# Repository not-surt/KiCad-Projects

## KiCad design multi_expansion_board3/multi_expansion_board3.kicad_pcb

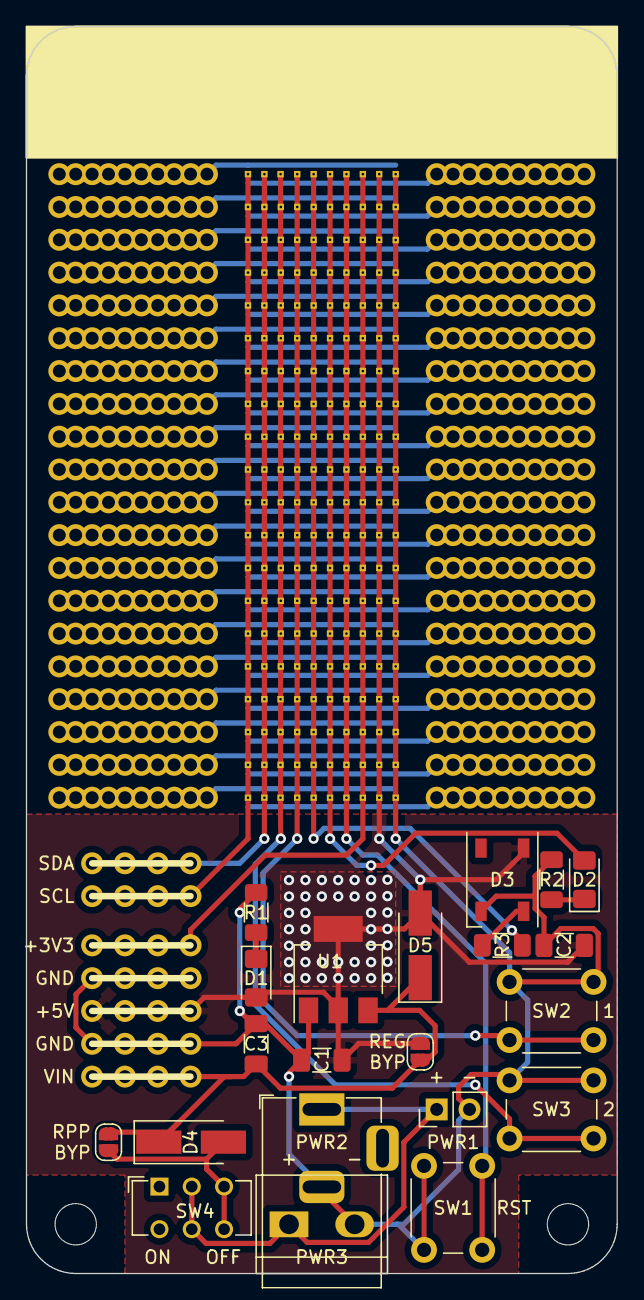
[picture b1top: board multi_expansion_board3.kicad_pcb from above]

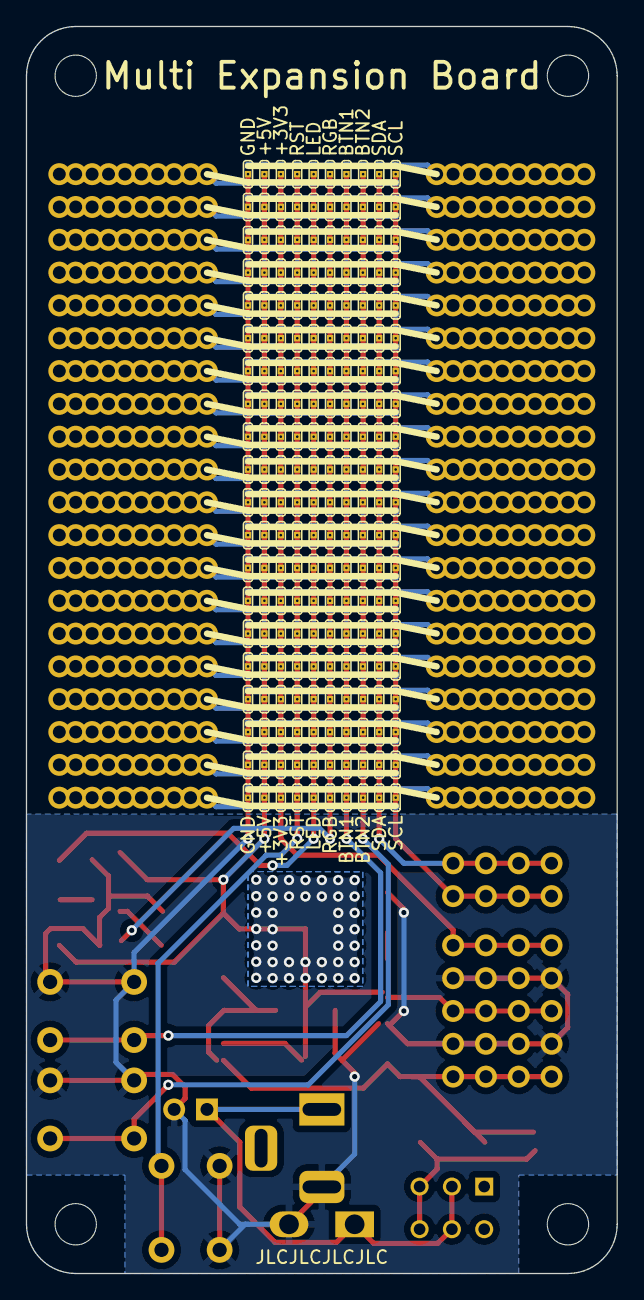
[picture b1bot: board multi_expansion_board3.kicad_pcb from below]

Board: 2 copper layers, 45.7 x 96.5 mm, 248 parts (200 on the bottom side), 56 nets.

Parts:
C1: 0.1uF; C_1206_3216Metric_Pad1.33x1.80mm_HandSolder
C2, C3: 10uF; C_1206_3216Metric_Pad1.33x1.80mm_HandSolder
D1, D2: LED; LED_1206_3216Metric_Pad1.42x1.75mm_HandSolder
D3: WS2812B; LED_WS2812B_PLCC4_5.0x5.0mm_P3.2mm
D4, D5: D; D_SMA_Handsoldering
J1, J2, J3, J4, J5, J6, J7, J8, J9, J10, J11, J12, J13, J14, J15, J16, J17, J18, J19, J20: Conn_01x20; PinHeader_1x20_P2.54mm_Vertical_No_Silk
J21, J22, J23, J24, J25, J26, J27: Conn_01x04; PinHeader_1x04_P2.54mm_Vertical_No_Silk
JP1, JP2: SolderJumper_2_Open; SolderJumper-2_P1.3mm_Open_RoundedPad1.0x1.5mm
JP3, JP4, JP5, JP6, JP7, JP8, JP9, JP10, JP11, JP12, JP13, JP14, JP15, JP16, JP17, JP18, JP19, JP20, JP21, JP22, JP23, JP24, JP25, JP26, JP27, JP28, JP29, JP30, JP31, JP32, JP33, JP34, JP35, JP36, JP37, JP38, JP39, JP40, JP41, JP42, JP43, JP44, JP45, JP46, JP47, JP48, JP49, JP50, JP51, JP52, JP53, JP54, JP55, JP56, JP57, JP58, JP59, JP60, JP61, JP62, JP63, JP64, JP65, JP66, JP67, JP68, JP69, JP70, JP71, JP72, JP73, JP74, JP75, JP76, JP77, JP78, JP79, JP80, JP81, JP82, JP83, JP84, JP85, JP86, JP87, JP88, JP89, JP90, JP91, JP92, JP93, JP94, JP95, JP96, JP97, JP98, JP99, JP100, JP101, JP102, JP103, JP104, JP105, JP106, JP107, JP108, JP109, JP110, JP111, JP112, JP113, JP114, JP115, JP116, JP117, JP118, JP119, JP120, JP121, JP122, JP123, JP124, JP125, JP126, JP127, JP128, JP129, JP130, JP131, JP132, JP133, JP134, JP135, JP136, JP137, JP138, JP139, JP140, JP141, JP142, JP143, JP144, JP145, JP146, JP147, JP148, JP149, JP150, JP151, JP152, JP153, JP154, JP155, JP156, JP157, JP158, JP159, JP160, JP161, JP162, JP163, JP164, JP165, JP166, JP167, JP168, JP169, JP170, JP171, JP172, JP173, JP174, JP175, JP176, JP177, JP178, JP179, JP180, JP181, JP182, JP183, JP184, JP185, JP186, JP187, JP188, JP189, JP190, JP191, JP192, JP193, JP194, JP195, JP196, JP197, JP198, JP199, JP200, JP201, JP202: SolderJumper_3_Open; SolderJumper-mini-3
PWR1: Conn_01x02; PinHeader_1x02_P2.54mm_Vertical
PWR2: Barrel_Jack; BarrelJack_Horizontal
PWR3: Screw_Terminal_01x02; TerminalBlock_bornier-2_P5.08mm
R1, R2: R; R_1206_3216Metric_Pad1.30x1.75mm_HandSolder
R3: 470R; R_1206_3216Metric_Pad1.30x1.75mm_HandSolder
SW1, SW2, SW3: SW_Push; SW_PUSH_6mm
SW4: SW_SPST; SW_CuK_JS202011CQN_DPDT_Straight
U1: AMS1117-5.0; SOT-223-3_TabPin2

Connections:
/+3V3: J25.1, J25.2, J25.3, J25.4, JP43.2 (C), JP44.2 (C), JP45.2 (C), JP46.2 (C), JP47.2 (C), JP48.2 (C), JP49.2 (C), JP50.2 (C), JP51.2 (C), JP52.2 (C), JP53.2 (C), JP54.2 (C), JP55.2 (C), JP56.2 (C), JP57.2 (C), JP58.2 (C), JP59.2 (C), JP60.2 (C), JP61.2 (C), JP62.2 (C)
/+5V: C1.2, C2.1, D1.2 (A), D3.1 (VDD), D5.2 (A), J24.1, J24.2, J24.3, J24.4, JP2.2 (B), JP3.2 (C), JP4.2 (C), JP5.2 (C), JP6.2 (C), JP7.2 (C), JP8.2 (C), JP9.2 (C), JP10.2 (C), JP11.2 (C), JP12.2 (C), JP13.2 (C), JP14.2 (C), JP15.2 (C), JP16.2 (C), JP17.2 (C), JP18.2 (C), JP19.2 (C), JP20.2 (C), JP21.2 (C), JP22.2 (C), U1.2 (VO)
/BTN1: JP83.2 (C), JP84.2 (C), JP85.2 (C), JP86.2 (C), JP87.2 (C), JP88.2 (C), JP89.2 (C), JP90.2 (C), JP91.2 (C), JP92.2 (C), JP93.2 (C), JP94.2 (C), JP95.2 (C), JP96.2 (C), JP97.2 (C), JP98.2 (C), JP99.2 (C), JP100.2 (C), JP101.2 (C), JP102.2 (C), SW2.2
/BTN2: JP183.2 (C), JP184.2 (C), JP185.2 (C), JP186.2 (C), JP187.2 (C), JP188.2 (C), JP189.2 (C), JP190.2 (C), JP191.2 (C), JP192.2 (C), JP193.2 (C), JP194.2 (C), JP195.2 (C), JP196.2 (C), JP197.2 (C), JP198.2 (C), JP199.2 (C), JP200.2 (C), JP201.2 (C), JP202.2 (C), SW3.2
/LED: D2.2 (A), JP63.2 (C), JP64.2 (C), JP65.2 (C), JP66.2 (C), JP67.2 (C), JP68.2 (C), JP69.2 (C), JP70.2 (C), JP71.2 (C), JP72.2 (C), JP73.2 (C), JP74.2 (C), JP75.2 (C), JP76.2 (C), JP77.2 (C), JP78.2 (C), JP79.2 (C), JP80.2 (C), JP81.2 (C), JP82.2 (C)
/RGB: JP103.2 (C), JP104.2 (C), JP105.2 (C), JP106.2 (C), JP107.2 (C), JP108.2 (C), JP109.2 (C), JP110.2 (C), JP111.2 (C), JP112.2 (C), JP113.2 (C), JP114.2 (C), JP115.2 (C), JP116.2 (C), JP117.2 (C), JP118.2 (C), JP119.2 (C), JP120.2 (C), JP121.2 (C), JP122.2 (C), R3.1
/RST: JP163.2 (C), JP164.2 (C), JP165.2 (C), JP166.2 (C), JP167.2 (C), JP168.2 (C), JP169.2 (C), JP170.2 (C), JP171.2 (C), JP172.2 (C), JP173.2 (C), JP174.2 (C), JP175.2 (C), JP176.2 (C), JP177.2 (C), JP178.2 (C), JP179.2 (C), JP180.2 (C), JP181.2 (C), JP182.2 (C), SW1.2
/SCL: J27.1, J27.2, J27.3, J27.4, JP143.2 (C), JP144.2 (C), JP145.2 (C), JP146.2 (C), JP147.2 (C), JP148.2 (C), JP149.2 (C), JP150.2 (C), JP151.2 (C), JP152.2 (C), JP153.2 (C), JP154.2 (C), JP155.2 (C), JP156.2 (C), JP157.2 (C), JP158.2 (C), JP159.2 (C), JP160.2 (C), JP161.2 (C), JP162.2 (C)
/SDA: J26.1, J26.2, J26.3, J26.4, JP123.2 (C), JP124.2 (C), JP125.2 (C), JP126.2 (C), JP127.2 (C), JP128.2 (C), JP129.2 (C), JP130.2 (C), JP131.2 (C), JP132.2 (C), JP133.2 (C), JP134.2 (C), JP135.2 (C), JP136.2 (C), JP137.2 (C), JP138.2 (C), JP139.2 (C), JP140.2 (C), JP141.2 (C), JP142.2 (C)
/VIN: C3.1, D4.1 (K), D5.1 (K), J23.1, J23.2, J23.3, J23.4, JP1.2 (B), JP2.1 (A), U1.3 (VI)
GND: C1.1, C2.2, C3.2, D3.3 (VSS), J21.1, J21.2, J21.3, J21.4, J22.1, J22.2, J22.3, J22.4, JP23.2 (C), JP24.2 (C), JP25.2 (C), JP26.2 (C), JP27.2 (C), JP28.2 (C), JP29.2 (C), JP30.2 (C), JP31.2 (C), JP32.2 (C), JP33.2 (C), JP34.2 (C), JP35.2 (C), JP36.2 (C), JP37.2 (C), JP38.2 (C), JP39.2 (C), JP40.2 (C), JP41.2 (C), JP42.2 (C), PWR1.2, PWR2.2, PWR3.2, R1.2, R2.2, SW1.1, SW2.1, SW3.1, U1.1 (GND)
unnamed: D1.1 (K), R1.1
unnamed: D2.1 (K), R2.1
unnamed: D3.4 (DIN), R3.2
unnamed: D4.2 (A), JP1.1 (A), SW4.3 (C), SW4.6 (C)
unnamed: PWR1.1, PWR2.1, PWR3.1, SW4.2 (B), SW4.5 (B)
Pin_1: J1.1, J2.1, J3.1, J4.1, J5.1, J6.1, J7.1, J8.1, J9.1, J10.1, JP3.1 (A), JP23.1 (A), JP43.1 (A), JP63.1 (A), JP83.1 (A), JP103.1 (A), JP123.1 (A), JP143.1 (A), JP163.1 (A), JP183.1 (A)
Pin_2: J1.2, J2.2, J3.2, J4.2, J5.2, J6.2, J7.2, J8.2, J9.2, J10.2, JP4.1 (A), JP24.1 (A), JP44.1 (A), JP64.1 (A), JP84.1 (A), JP104.1 (A), JP124.1 (A), JP144.1 (A), JP164.1 (A), JP184.1 (A)
Pin_3: J1.3, J2.3, J3.3, J4.3, J5.3, J6.3, J7.3, J8.3, J9.3, J10.3, JP5.1 (A), JP25.1 (A), JP45.1 (A), JP65.1 (A), JP85.1 (A), JP105.1 (A), JP125.1 (A), JP145.1 (A), JP165.1 (A), JP185.1 (A)
Pin_4: J1.4, J2.4, J3.4, J4.4, J5.4, J6.4, J7.4, J8.4, J9.4, J10.4, JP6.1 (A), JP26.1 (A), JP46.1 (A), JP66.1 (A), JP86.1 (A), JP106.1 (A), JP126.1 (A), JP146.1 (A), JP166.1 (A), JP186.1 (A)
Pin_5: J1.5, J2.5, J3.5, J4.5, J5.5, J6.5, J7.5, J8.5, J9.5, J10.5, JP7.1 (A), JP27.1 (A), JP47.1 (A), JP67.1 (A), JP87.1 (A), JP107.1 (A), JP127.1 (A), JP147.1 (A), JP167.1 (A), JP187.1 (A)
Pin_6: J1.6, J2.6, J3.6, J4.6, J5.6, J6.6, J7.6, J8.6, J9.6, J10.6, JP8.1 (A), JP28.1 (A), JP48.1 (A), JP68.1 (A), JP88.1 (A), JP108.1 (A), JP128.1 (A), JP148.1 (A), JP168.1 (A), JP188.1 (A)
Pin_7: J1.7, J2.7, J3.7, J4.7, J5.7, J6.7, J7.7, J8.7, J9.7, J10.7, JP9.1 (A), JP29.1 (A), JP49.1 (A), JP69.1 (A), JP89.1 (A), JP109.1 (A), JP129.1 (A), JP149.1 (A), JP169.1 (A), JP189.1 (A)
Pin_8: J1.8, J2.8, J3.8, J4.8, J5.8, J6.8, J7.8, J8.8, J9.8, J10.8, JP10.1 (A), JP30.1 (A), JP50.1 (A), JP70.1 (A), JP90.1 (A), JP110.1 (A), JP130.1 (A), JP150.1 (A), JP170.1 (A), JP190.1 (A)
Pin_9: J1.9, J2.9, J3.9, J4.9, J5.9, J6.9, J7.9, J8.9, J9.9, J10.9, JP11.1 (A), JP31.1 (A), JP51.1 (A), JP71.1 (A), JP91.1 (A), JP111.1 (A), JP131.1 (A), JP151.1 (A), JP171.1 (A), JP191.1 (A)
Pin_10: J1.10, J2.10, J3.10, J4.10, J5.10, J6.10, J7.10, J8.10, J9.10, J10.10, JP12.1 (A), JP32.1 (A), JP52.1 (A), JP72.1 (A), JP92.1 (A), JP112.1 (A), JP132.1 (A), JP152.1 (A), JP172.1 (A), JP192.1 (A)
Pin_11: J1.11, J2.11, J3.11, J4.11, J5.11, J6.11, J7.11, J8.11, J9.11, J10.11, JP13.1 (A), JP33.1 (A), JP53.1 (A), JP73.1 (A), JP93.1 (A), JP113.1 (A), JP133.1 (A), JP153.1 (A), JP173.1 (A), JP193.1 (A)
Pin_12: J1.12, J2.12, J3.12, J4.12, J5.12, J6.12, J7.12, J8.12, J9.12, J10.12, JP14.1 (A), JP34.1 (A), JP54.1 (A), JP74.1 (A), JP94.1 (A), JP114.1 (A), JP134.1 (A), JP154.1 (A), JP174.1 (A), JP194.1 (A)
Pin_13: J1.13, J2.13, J3.13, J4.13, J5.13, J6.13, J7.13, J8.13, J9.13, J10.13, JP15.1 (A), JP35.1 (A), JP55.1 (A), JP75.1 (A), JP95.1 (A), JP115.1 (A), JP135.1 (A), JP155.1 (A), JP175.1 (A), JP195.1 (A)
Pin_14: J1.14, J2.14, J3.14, J4.14, J5.14, J6.14, J7.14, J8.14, J9.14, J10.14, JP16.1 (A), JP36.1 (A), JP56.1 (A), JP76.1 (A), JP96.1 (A), JP116.1 (A), JP136.1 (A), JP156.1 (A), JP176.1 (A), JP196.1 (A)
Pin_15: J1.15, J2.15, J3.15, J4.15, J5.15, J6.15, J7.15, J8.15, J9.15, J10.15, JP17.1 (A), JP37.1 (A), JP57.1 (A), JP77.1 (A), JP97.1 (A), JP117.1 (A), JP137.1 (A), JP157.1 (A), JP177.1 (A), JP197.1 (A)
Pin_16: J1.16, J2.16, J3.16, J4.16, J5.16, J6.16, J7.16, J8.16, J9.16, J10.16, JP18.1 (A), JP38.1 (A), JP58.1 (A), JP78.1 (A), JP98.1 (A), JP118.1 (A), JP138.1 (A), JP158.1 (A), JP178.1 (A), JP198.1 (A)
Pin_17: J1.17, J2.17, J3.17, J4.17, J5.17, J6.17, J7.17, J8.17, J9.17, J10.17, JP19.1 (A), JP39.1 (A), JP59.1 (A), JP79.1 (A), JP99.1 (A), JP119.1 (A), JP139.1 (A), JP159.1 (A), JP179.1 (A), JP199.1 (A)
Pin_18: J1.18, J2.18, J3.18, J4.18, J5.18, J6.18, J7.18, J8.18, J9.18, J10.18, JP20.1 (A), JP40.1 (A), JP60.1 (A), JP80.1 (A), JP100.1 (A), JP120.1 (A), JP140.1 (A), JP160.1 (A), JP180.1 (A), JP200.1 (A)
Pin_19: J1.19, J2.19, J3.19, J4.19, J5.19, J6.19, J7.19, J8.19, J9.19, J10.19, JP21.1 (A), JP41.1 (A), JP61.1 (A), JP81.1 (A), JP101.1 (A), JP121.1 (A), JP141.1 (A), JP161.1 (A), JP181.1 (A), JP201.1 (A)
Pin_20: J1.20, J2.20, J3.20, J4.20, J5.20, J6.20, J7.20, J8.20, J9.20, J10.20, JP22.1 (A), JP42.1 (A), JP62.1 (A), JP82.1 (A), JP102.1 (A), JP122.1 (A), JP142.1 (A), JP162.1 (A), JP182.1 (A), JP202.1 (A)
Pin_21: J11.20, J12.20, J13.20, J14.20, J15.20, J16.20, J17.20, J18.20, J19.20, J20.20, JP22.3 (B), JP42.3 (B), JP62.3 (B), JP82.3 (B), JP102.3 (B), JP122.3 (B), JP142.3 (B), JP162.3 (B), JP182.3 (B), JP202.3 (B)
Pin_22: J11.19, J12.19, J13.19, J14.19, J15.19, J16.19, J17.19, J18.19, J19.19, J20.19, JP21.3 (B), JP41.3 (B), JP61.3 (B), JP81.3 (B), JP101.3 (B), JP121.3 (B), JP141.3 (B), JP161.3 (B), JP181.3 (B), JP201.3 (B)
Pin_23: J11.18, J12.18, J13.18, J14.18, J15.18, J16.18, J17.18, J18.18, J19.18, J20.18, JP20.3 (B), JP40.3 (B), JP60.3 (B), JP80.3 (B), JP100.3 (B), JP120.3 (B), JP140.3 (B), JP160.3 (B), JP180.3 (B), JP200.3 (B)
Pin_24: J11.17, J12.17, J13.17, J14.17, J15.17, J16.17, J17.17, J18.17, J19.17, J20.17, JP19.3 (B), JP39.3 (B), JP59.3 (B), JP79.3 (B), JP99.3 (B), JP119.3 (B), JP139.3 (B), JP159.3 (B), JP179.3 (B), JP199.3 (B)
Pin_25: J11.16, J12.16, J13.16, J14.16, J15.16, J16.16, J17.16, J18.16, J19.16, J20.16, JP18.3 (B), JP38.3 (B), JP58.3 (B), JP78.3 (B), JP98.3 (B), JP118.3 (B), JP138.3 (B), JP158.3 (B), JP178.3 (B), JP198.3 (B)
Pin_26: J11.15, J12.15, J13.15, J14.15, J15.15, J16.15, J17.15, J18.15, J19.15, J20.15, JP17.3 (B), JP37.3 (B), JP57.3 (B), JP77.3 (B), JP97.3 (B), JP117.3 (B), JP137.3 (B), JP157.3 (B), JP177.3 (B), JP197.3 (B)
Pin_27: J11.14, J12.14, J13.14, J14.14, J15.14, J16.14, J17.14, J18.14, J19.14, J20.14, JP16.3 (B), JP36.3 (B), JP56.3 (B), JP76.3 (B), JP96.3 (B), JP116.3 (B), JP136.3 (B), JP156.3 (B), JP176.3 (B), JP196.3 (B)
Pin_28: J11.13, J12.13, J13.13, J14.13, J15.13, J16.13, J17.13, J18.13, J19.13, J20.13, JP15.3 (B), JP35.3 (B), JP55.3 (B), JP75.3 (B), JP95.3 (B), JP115.3 (B), JP135.3 (B), JP155.3 (B), JP175.3 (B), JP195.3 (B)
Pin_29: J11.12, J12.12, J13.12, J14.12, J15.12, J16.12, J17.12, J18.12, J19.12, J20.12, JP14.3 (B), JP34.3 (B), JP54.3 (B), JP74.3 (B), JP94.3 (B), JP114.3 (B), JP134.3 (B), JP154.3 (B), JP174.3 (B), JP194.3 (B)
Pin_30: J11.11, J12.11, J13.11, J14.11, J15.11, J16.11, J17.11, J18.11, J19.11, J20.11, JP13.3 (B), JP33.3 (B), JP53.3 (B), JP73.3 (B), JP93.3 (B), JP113.3 (B), JP133.3 (B), JP153.3 (B), JP173.3 (B), JP193.3 (B)
Pin_31: J11.10, J12.10, J13.10, J14.10, J15.10, J16.10, J17.10, J18.10, J19.10, J20.10, JP12.3 (B), JP32.3 (B), JP52.3 (B), JP72.3 (B), JP92.3 (B), JP112.3 (B), JP132.3 (B), JP152.3 (B), JP172.3 (B), JP192.3 (B)
Pin_32: J11.9, J12.9, J13.9, J14.9, J15.9, J16.9, J17.9, J18.9, J19.9, J20.9, JP11.3 (B), JP31.3 (B), JP51.3 (B), JP71.3 (B), JP91.3 (B), JP111.3 (B), JP131.3 (B), JP151.3 (B), JP171.3 (B), JP191.3 (B)
Pin_33: J11.8, J12.8, J13.8, J14.8, J15.8, J16.8, J17.8, J18.8, J19.8, J20.8, JP10.3 (B), JP30.3 (B), JP50.3 (B), JP70.3 (B), JP90.3 (B), JP110.3 (B), JP130.3 (B), JP150.3 (B), JP170.3 (B), JP190.3 (B)
Pin_34: J11.7, J12.7, J13.7, J14.7, J15.7, J16.7, J17.7, J18.7, J19.7, J20.7, JP9.3 (B), JP29.3 (B), JP49.3 (B), JP69.3 (B), JP89.3 (B), JP109.3 (B), JP129.3 (B), JP149.3 (B), JP169.3 (B), JP189.3 (B)
Pin_35: J11.6, J12.6, J13.6, J14.6, J15.6, J16.6, J17.6, J18.6, J19.6, J20.6, JP8.3 (B), JP28.3 (B), JP48.3 (B), JP68.3 (B), JP88.3 (B), JP108.3 (B), JP128.3 (B), JP148.3 (B), JP168.3 (B), JP188.3 (B)
Pin_36: J11.5, J12.5, J13.5, J14.5, J15.5, J16.5, J17.5, J18.5, J19.5, J20.5, JP7.3 (B), JP27.3 (B), JP47.3 (B), JP67.3 (B), JP87.3 (B), JP107.3 (B), JP127.3 (B), JP147.3 (B), JP167.3 (B), JP187.3 (B)
Pin_37: J11.4, J12.4, J13.4, J14.4, J15.4, J16.4, J17.4, J18.4, J19.4, J20.4, JP6.3 (B), JP26.3 (B), JP46.3 (B), JP66.3 (B), JP86.3 (B), JP106.3 (B), JP126.3 (B), JP146.3 (B), JP166.3 (B), JP186.3 (B)
Pin_38: J11.3, J12.3, J13.3, J14.3, J15.3, J16.3, J17.3, J18.3, J19.3, J20.3, JP5.3 (B), JP25.3 (B), JP45.3 (B), JP65.3 (B), JP85.3 (B), JP105.3 (B), JP125.3 (B), JP145.3 (B), JP165.3 (B), JP185.3 (B)
Pin_39: J11.2, J12.2, J13.2, J14.2, J15.2, J16.2, J17.2, J18.2, J19.2, J20.2, JP4.3 (B), JP24.3 (B), JP44.3 (B), JP64.3 (B), JP84.3 (B), JP104.3 (B), JP124.3 (B), JP144.3 (B), JP164.3 (B), JP184.3 (B)
Pin_40: J11.1, J12.1, J13.1, J14.1, J15.1, J16.1, J17.1, J18.1, J19.1, J20.1, JP3.3 (B), JP23.3 (B), JP43.3 (B), JP63.3 (B), JP83.3 (B), JP103.3 (B), JP123.3 (B), JP143.3 (B), JP163.3 (B), JP183.3 (B)
